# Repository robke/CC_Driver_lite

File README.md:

# CC_Driver_lite
Simple programable LED CC driver

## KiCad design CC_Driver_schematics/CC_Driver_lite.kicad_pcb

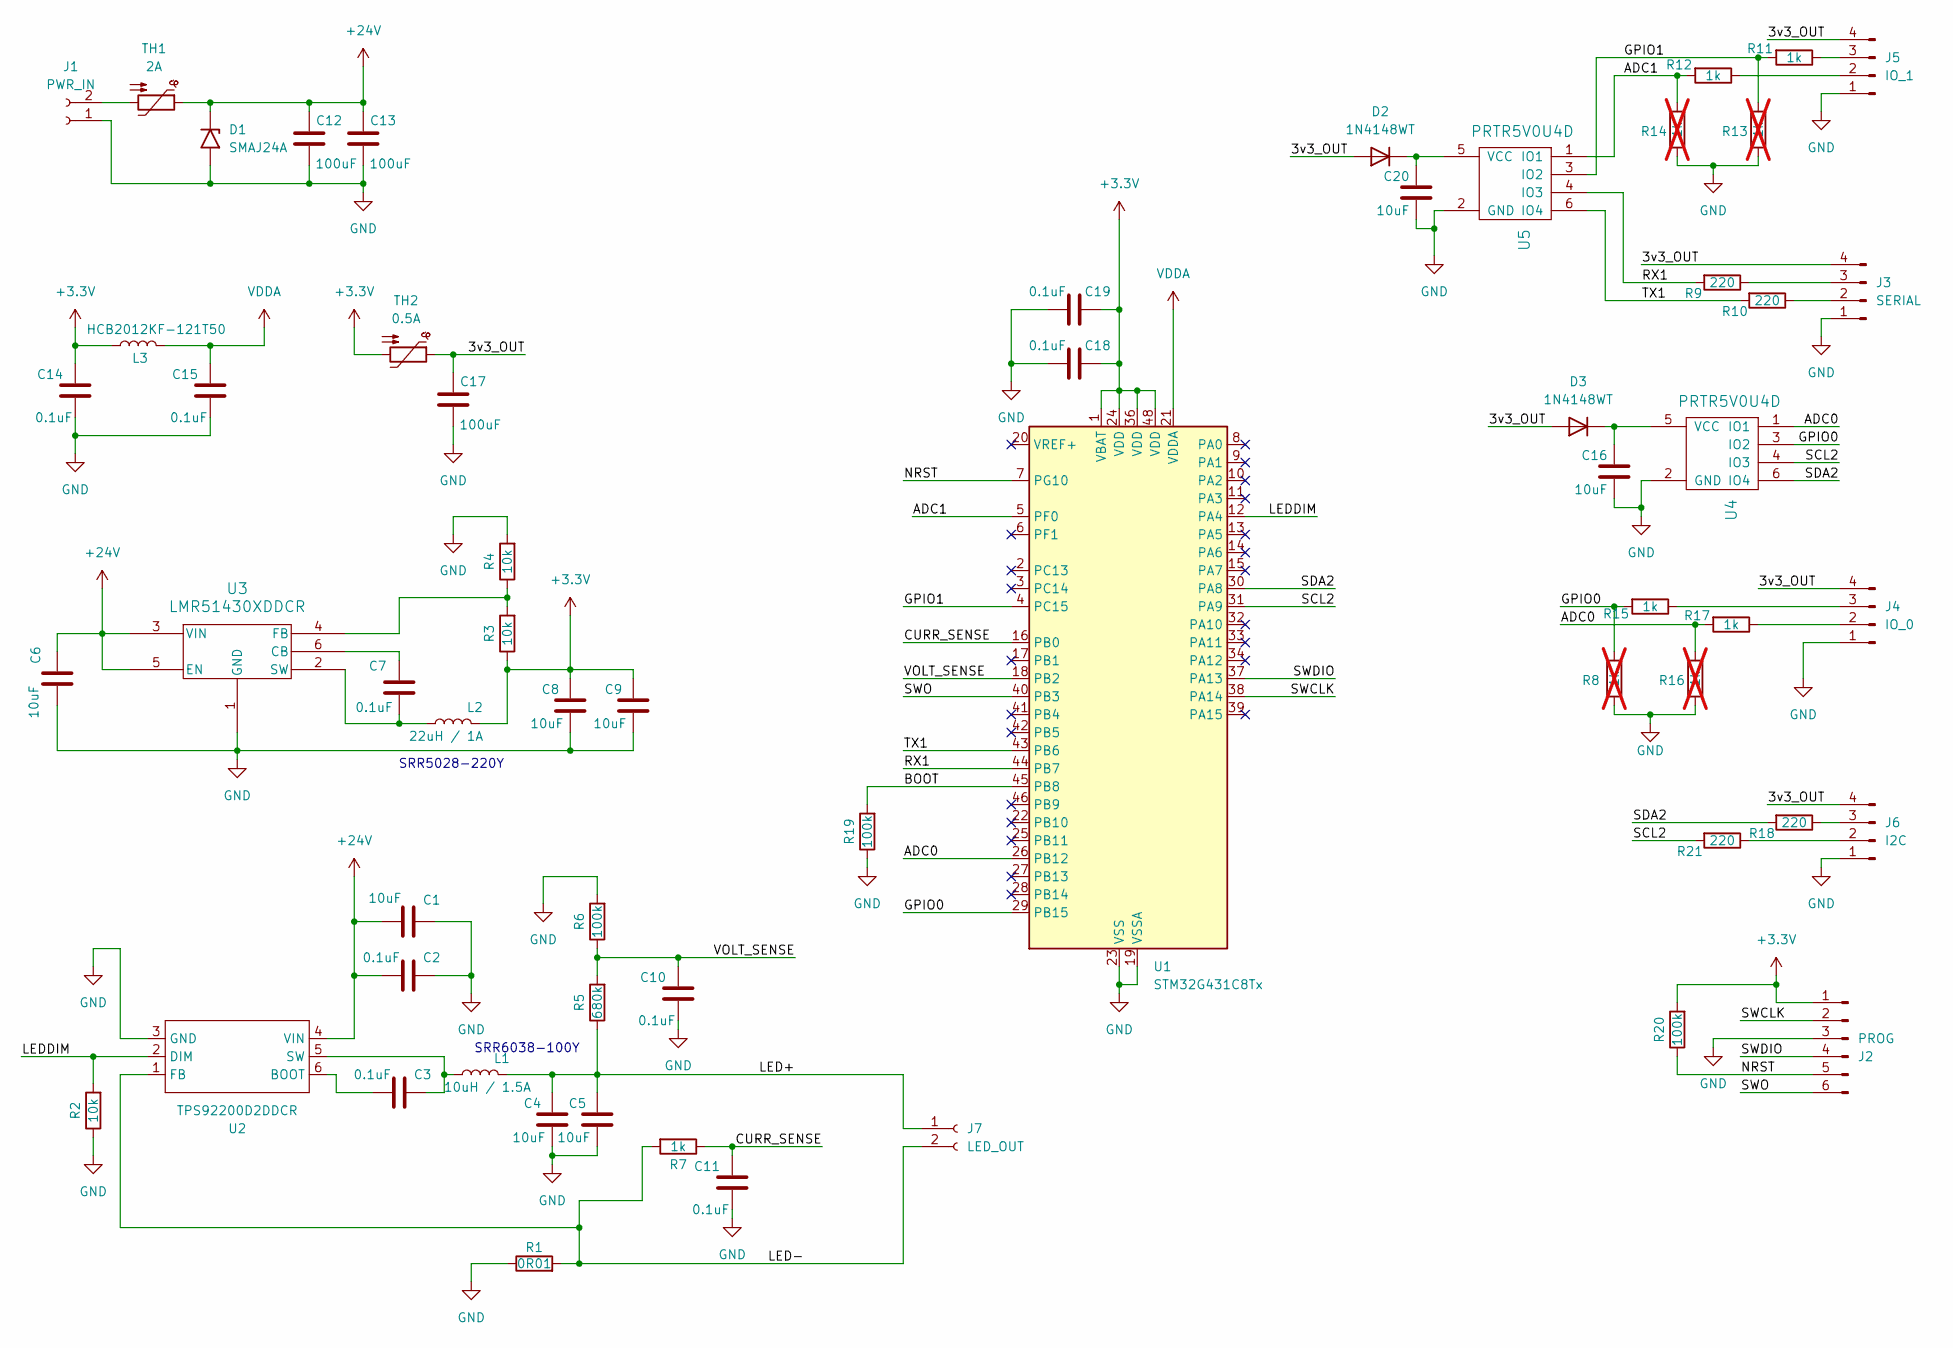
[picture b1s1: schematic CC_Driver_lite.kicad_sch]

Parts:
C1, C6, C8, C9, C16, C20: 10uF; C_0603_1608Metric_Pad1.08x0.95mm_HandSolder
C2, C3, C7, C10, C11, C14, C15, C18, C19: 0.1uF; C_0603_1608Metric_Pad1.08x0.95mm_HandSolder
C4, C5: 10uF; C_0805_2012Metric_Pad1.18x1.45mm_HandSolder
C12, C13, C17: 100uF; C_1206_3216Metric
D1: SMAJ24A; D_SMA
D2, D3: 1N4148WT; D_SOD-523
J1: PWR_IN; TerminalBlock_MetzConnect_Type011_RT05502HBWC_1x02_P5.00mm_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
J2: PROG; PinSocket_1x06_P2.54mm_Vertical
J3: SERIAL; JST_PH_B4B-PH-K_1x04_P2.00mm_Vertical
J4: IO_0; JST_PH_B4B-PH-K_1x04_P2.00mm_Vertical
J5: IO_1; JST_PH_B4B-PH-K_1x04_P2.00mm_Vertical
J6: I2C; JST_PH_B4B-PH-K_1x04_P2.00mm_Vertical
J7: LED_OUT; TerminalBlock_MetzConnect_Type011_RT05502HBWC_1x02_P5.00mm_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
L1: 10uH / 1.5A; IND_BOURNS_SRR6038
L2: 22uH / 1A; IND_BOURNS_SRR5028
L3: HCB2012KF-121T50; L_0805_2012Metric_Pad1.05x1.20mm_HandSolder
R1: 0R01; R_2010_5025Metric
R2, R3, R4: 10k; R_0603_1608Metric_Pad0.98x0.95mm_HandSolder
R5: 680k; R_0603_1608Metric_Pad0.98x0.95mm_HandSolder
R6, R19, R20: 100k; R_0603_1608Metric_Pad0.98x0.95mm_HandSolder
R7, R11, R12, R15, R17: 1k; R_0603_1608Metric_Pad0.98x0.95mm_HandSolder
R8, R13, R14, R16: 1k; R_0603_1608Metric_Pad0.98x0.95mm_HandSolder; not fitted
R9, R10, R18, R21: 220; R_0603_1608Metric_Pad0.98x0.95mm_HandSolder
TH1: 2A; C_1206_3216Metric
TH2: 0.5A; C_1206_3216Metric
U1: STM32G431C8Tx; LQFP-48_7x7mm_P0.5mm
U2: TPS92200D2DDCR; TSOT-23-6_HandSoldering
U3: LMR51430XDDCR; TSOT-23-6_HandSoldering
U4, U5: PRTR5V0U4D; TSOP-6_1.65x3.05mm_P0.95mm

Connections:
+3.3V: C8.2, C9.2, C14.2, C18.2, C19.2, J2.1, L2.2, L3.1, R3.1, R20.2, TH2.2, U1.1 (VBAT), U1.24 (VDD), U1.36 (VDD), U1.48 (VDD)
+24V: C1.1, C2.1, C6.2, C12.2, C13.2, D1.1 (A1), TH1.1, U2.4 (VIN), U3.3 (VIN), U3.5 (EN)
/3v3_OUT: C17.2, D2.2 (A), D3.2 (A), J3.4, J4.4, J5.4, J6.4, TH2.1
/ADC0: R16.1, R17.2, U1.26 (PB12), U4.1 (IO1)
/ADC1: R12.2, R14.1, U1.5 (PF0), U5.1 (IO1)
/BOOT: R19.2, U1.45 (PB8)
/CURR_SENSE: C11.2, R7.1, U1.16 (PB0)
/GPIO0: R8.1, R15.2, U1.29 (PB15), U4.3 (IO2)
/GPIO1: R11.2, R13.1, U1.4 (PC15), U5.3 (IO2)
/LED+: C4.2, C5.2, J7.1, L1.2, R5.1
/LED-: J7.2, R1.2, R7.2, U2.1 (FB)
/LEDDIM: R2.2, U1.12 (PA4), U2.2 (DIM)
/NRST: J2.5, R20.1, U1.7 (PG10)
/RX1: R9.2, U1.44 (PB7), U5.4 (IO3)
/SCL2: R21.2, U1.31 (PA9), U4.4 (IO3)
/SDA2: R18.2, U1.30 (PA8), U4.6 (IO4)
/SWCLK: J2.2, U1.38 (PA14)
/SWDIO: J2.4, U1.37 (PA13)
/SWO: J2.6, U1.40 (PB3)
/TX1: R10.2, U1.43 (PB6), U5.6 (IO4)
/VOLT_SENSE: C10.2, R5.2, R6.1, U1.18 (PB2)
GND: C1.2, C2.2, C4.1, C5.1, C6.1, C8.1, C9.1, C10.1, C11.1, C12.1, C13.1, C14.1, C15.1, C16.1, C17.1, C18.1, C19.1, C20.1, D1.2 (A2), J1.1, J2.3, J3.1, J4.1, J5.1, J6.1, R1.1, R2.1, R4.2, R6.2, R8.2, R13.2, R14.2, R16.2, R19.1, U1.19 (VSSA), U1.23 (VSS), U1.35 (VSS), U1.47 (VSS), U2.3 (GND), U3.1 (GND), U4.2 (GND), U5.2 (GND)
unnamed: C20.2, D2.1 (K), U5.5 (VCC)
unnamed: C16.2, D3.1 (K), U4.5 (VCC)
unnamed: J1.2, TH1.2
unnamed: J3.2, R10.1
unnamed: J3.3, R9.1
unnamed: J4.2, R17.1
unnamed: J4.3, R15.1
unnamed: J5.2, R12.1
unnamed: J5.3, R11.1
unnamed: J6.2, R21.1
unnamed: J6.3, R18.1
unnamed: C3.1, U2.6 (BOOT)
unnamed: C3.2, L1.1, U2.5 (SW)
unnamed: C7.2, U3.6 (CB)
unnamed: R3.2, R4.1, U3.4 (FB)
unnamed: C7.1, L2.1, U3.2 (SW)
VDDA: C15.2, L3.2, U1.21 (VDDA)

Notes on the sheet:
SRR5028-220Y
SRR6038-100Y

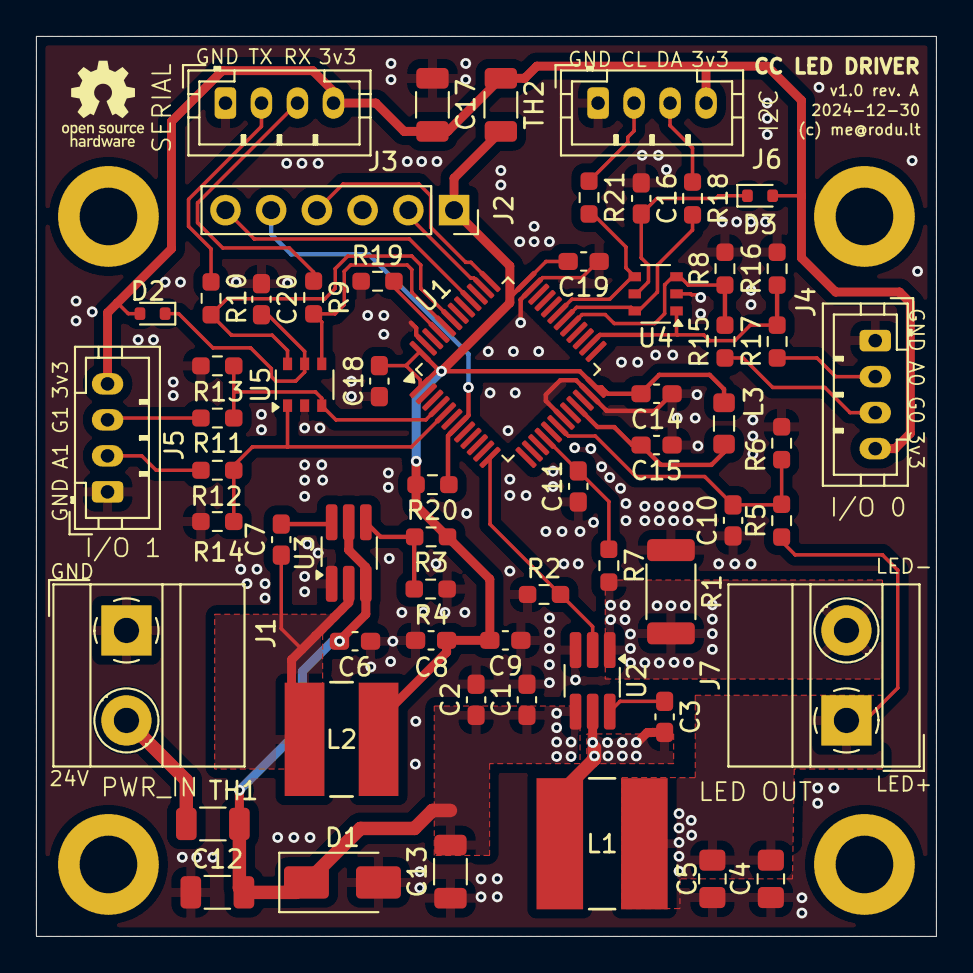
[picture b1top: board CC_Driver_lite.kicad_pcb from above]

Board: 2 copper layers, 50.0 x 50.0 mm, 61 parts (0 on the bottom side), 39 nets.

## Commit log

2025-01-02 Initial
